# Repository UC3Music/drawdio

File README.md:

# Drawdio

UC3Music version of Drawdio, originally designed by Jay Silver

Double side copper board, big and spacy pads (ready for first-time soldering)

*Uc3Music's enchancement: New output stage to provide twice output voltage and raise volume.*

---------------------------------------

Versión UC3Music del Drawdio, diseñado originalmente por Jay Silver

PCB de doble cara, pads grandes y espaciados (facil de soldar por noveles)

*Mejora de UC3Music: nueva etapa de salida que proporciona el doble de voltaje de salida para conseguir más volumen de salida.*

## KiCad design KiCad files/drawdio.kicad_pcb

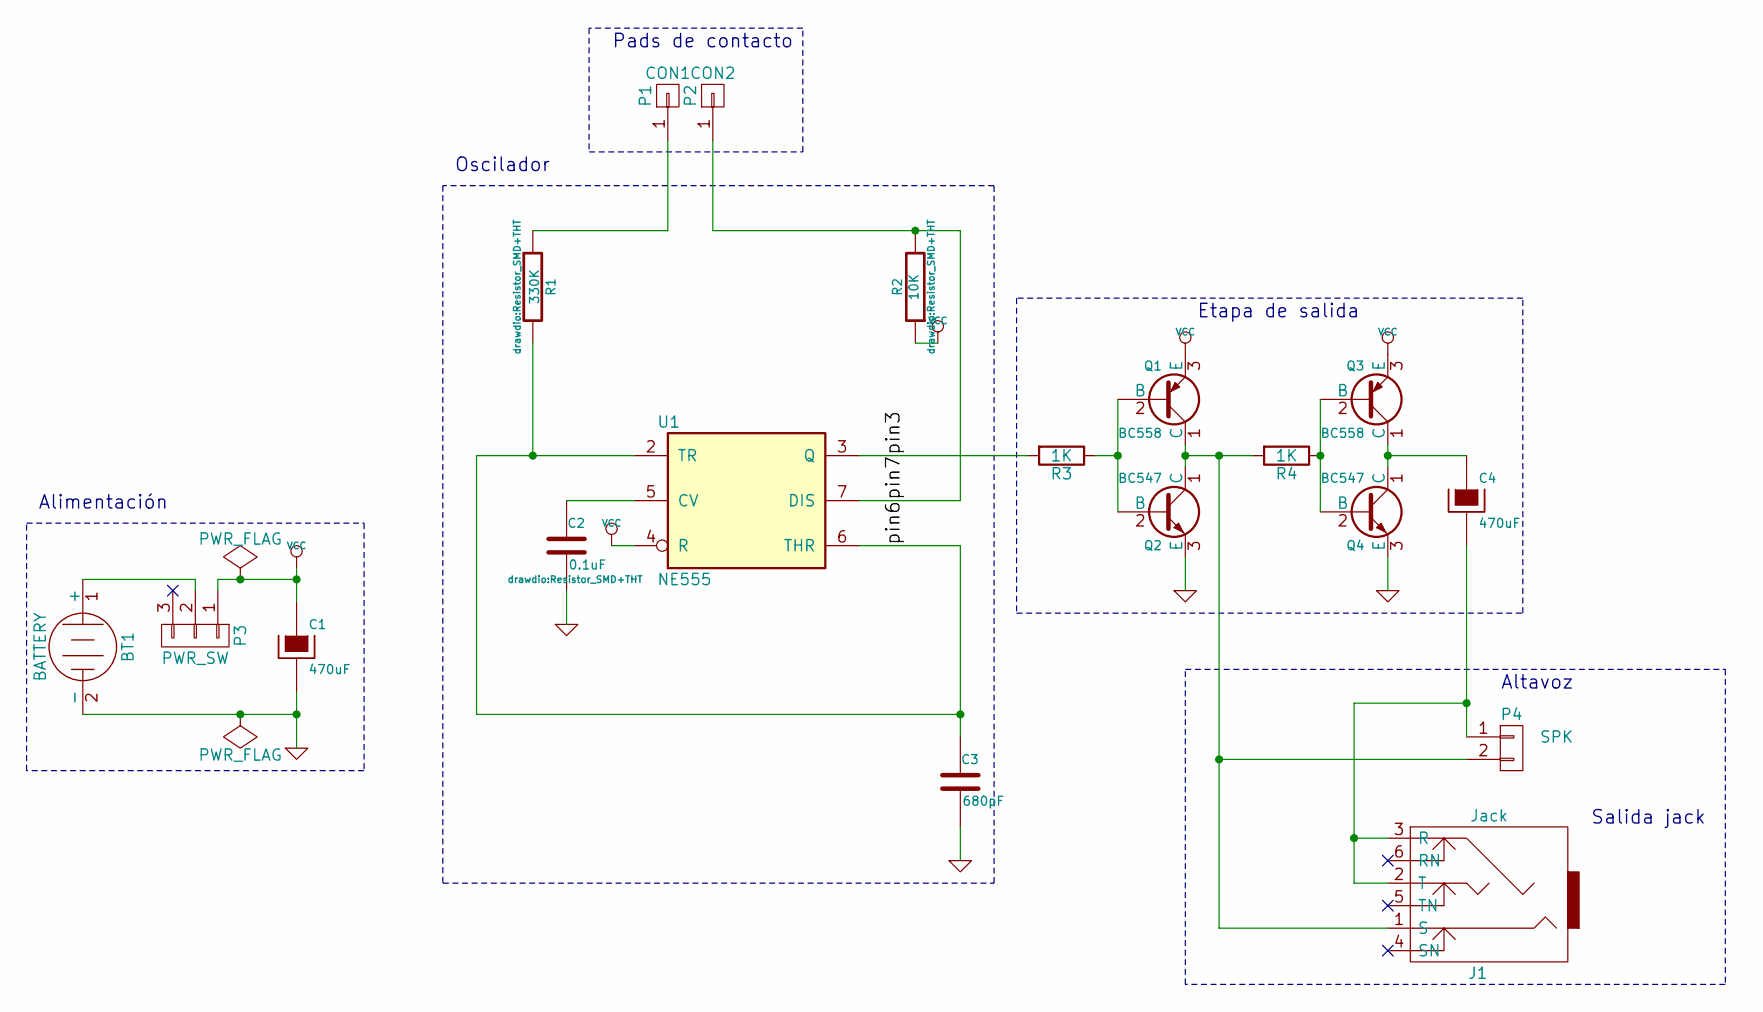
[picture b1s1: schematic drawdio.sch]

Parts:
BT1: BATTERY; AAA_cell_holder
C1, C4: 470uF; Elko_vert_11.2x6.3mm_RM2.5
C2: 0.1uF; Resistor_SMD+THT
C3: 680pF; Resistor_SMD+THT
J1: Jack; jack_barato
P1: CON1; Drawdio_conn
P2: CON2; Drawdio_conn
P3: PWR_SW; PWR_SW_Drawdio_SS-12D00(1P2T)
P4: SPK; RS_mini_speaker_724-3100
Q1, Q3: BC558; TO-92_JorFru_compact
Q2, Q4: BC547; TO-92_JorFru_compact
R1: 330K; Resistor_SMD+THT
R2: 10K; Resistor_SMD+THT
R3, R4: 1K; Resistor_SMD+THT
U1: NE555; DIP8+SOIC8_2

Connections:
/pin3: R3.2, U1.3 (Q)
/pin6: C3.1, R1.2, U1.2 (TR), U1.6 (THR)
/pin7: P2.1, R2.2, U1.7 (DIS)
GND: BT1.2 (-), C1.2, C2.2, C3.2, Q2.3 (E), Q4.3 (E), U1.1 (GND)
unnamed 4: BT1.1 (+), P3.2; also elsewhere on the board
unnamed: C2.1, U1.5 (CV)
unnamed: C4.1, Q3.1 (C), Q4.1 (C)
unnamed: C4.2, J1.2 (T), J1.3 (R), P4.1
unnamed: J1.1 (S), P4.2, Q1.1 (C), Q2.1 (C), R4.2
unnamed: P1.1, R1.1
unnamed: Q1.2 (B), Q2.2 (B), R3.1
unnamed: Q3.2 (B), Q4.2 (B), R4.1
VCC: C1.1, P3.1, Q1.3 (E), Q3.3 (E), R2.1, U1.4 (R), U1.8 (VCC); also elsewhere on the board

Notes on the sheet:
Altavoz
Etapa de salida
Alimentación
Pads de contacto
Oscilador
Salida jack

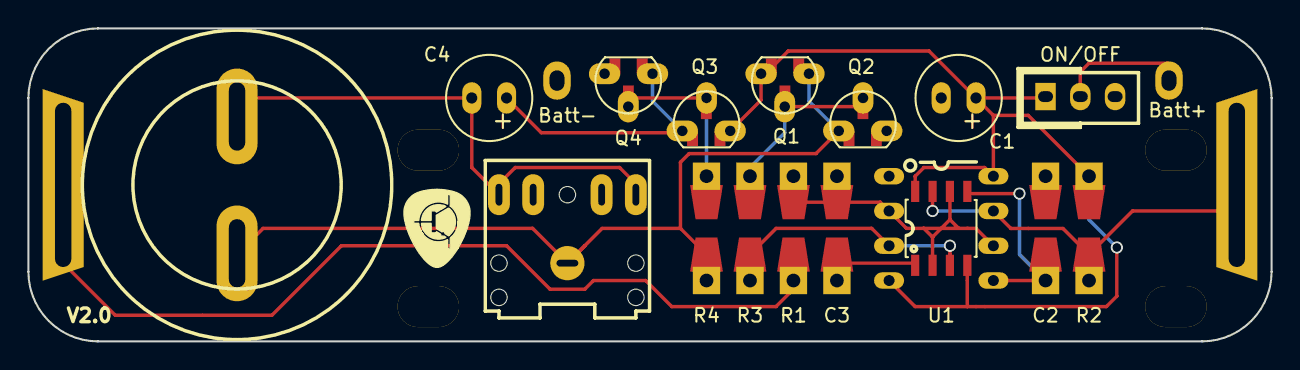
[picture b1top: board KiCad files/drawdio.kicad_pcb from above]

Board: 2 copper layers, 90.8 x 22.9 mm, 20 parts (0 on the bottom side), 13 nets.

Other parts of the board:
ON/OFF: PWR_SW; PWR_SW_Drawdio_SS-12D00(1P2T)
SPK: LOGO; Fiducial_1mm_Dia_2.54mm_Outer_CopperTop

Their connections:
unnamed 4: ON/OFF.2; also elsewhere on the board
VCC: ON/OFF.1; also elsewhere on the board

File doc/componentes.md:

# Condensadores
* C1 470uF
* C2 0.1uF
* C3 680pF
* C4 470uF

# Resistencias
* R1 330K o similar
* R2 10K
* R3, R4 1K

# Transistores
* Q2, Q4 BC547
* Q1, Q3 BC558/7

# Otros
* Muelle del portapilas hacia el lado contrario del altavoz
* Altavoz sin polaridad

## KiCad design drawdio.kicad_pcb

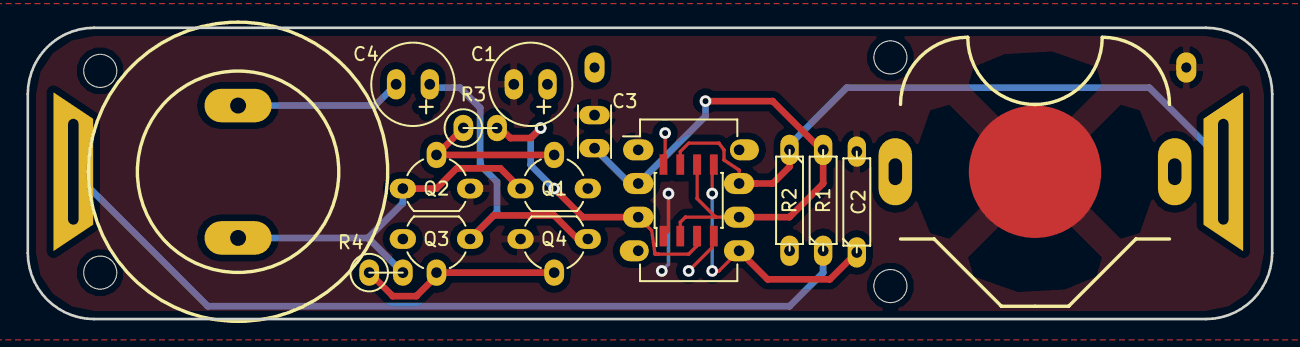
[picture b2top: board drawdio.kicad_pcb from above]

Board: 2 copper layers, 94.0 x 22.0 mm, 23 parts (0 on the bottom side), 12 nets.

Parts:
BT1: BATTERY; CR2025_Keystone_3002_button_cell_holder_SMT
C1, C4: CP; Elko_vert_11.2x6.3mm_RM2.5
C2: C; R3
C3: C; C_Rect_L4_W2.5_P2.5
P1, P2: CONN_01X01; Drawdio_conn
P3, P5, P6, P7: CONN_01X01; MountingHole_2-5mm
P4: CONN_01X02; RS_mini_speaker_724-3100
P9: CONN_02X04; SOIC-8_3.9x4.9mm_Pitch1.27mm
P10: CONN_01X02; AAA_cell_holder
Q1, Q3: BC558; TO-92_Molded_Wide_Oval
Q2, Q4: BC547; TO-92_Molded_Wide_Oval
R1, R2: R; R3
R3, R4: R; R1
U1: LM555N; DIP-8_W7.62mm_LongPads

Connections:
/pin2: C3.1, P9.2, P9.6, R1.2, U1.2, U1.6
/pin3: P9.3, R3.2, U1.3
/pin5: C2.1, P9.5, U1.5
/pin7: P2.1, P9.7, R2.1, U1.7
GND: BT1.2, C1.2, C2.2, C3.2, P9.1, P10.1, Q2.3, Q4.3, U1.1
unnamed: C4.1, Q3.1, Q4.1
unnamed: C4.2, P4.1
unnamed: P1.1, R1.1
unnamed: P4.2, Q1.1, Q2.1, R4.2
unnamed: Q1.2, Q2.2, R3.1
unnamed: Q3.2, Q4.2, R4.1
VCC: BT1.1, C1.1, P9.4, P9.8, P10.2, Q1.3, Q3.3, R2.2, U1.4, U1.8

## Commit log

2015-06-16 prototipo versión amatacaballo
2015-06-16 gerbers add
2015-09-05 Bigger pads for easier soldering
2015-09-05 Trigged size
2015-09-07 smaller board
2015-09-07 V0.2
2015-09-09 added README file
2015-09-09 readme revision
2015-09-09 media revision
2015-09-10 Updated README.md to show image
2015-09-10 Fix ugly track
2015-09-10 Add GND plane in front layer
2015-09-18 Fixed ugly traces
2015-09-18 Update gerbers
2015-10-19 Heavy work
2015-10-19 Added holes
2015-10-27 Añadidas resistencias
2015-10-27 AAA cell added
2015-10-27 Pre-release 1.0
2015-10-28 Reviewed and ready
2015-10-28 Gerbers sent
2015-11-02 Updated README and media folder
2015-11-02 Fixed image
2015-11-02 fixed route
2015-11-15 Wiki is coming
2015-11-15 files moved to folders
2017-01-20 schematic upgrades
2017-01-20 added parts lists with links to RS casta-todavia
2017-01-23 Checkpoint, a dormir!
2017-01-23 Adeed Jack
2017-01-23 Redimensionada
2017-01-25 puede que funcione
2017-01-25 Mounting holes
2017-01-26 Casi terminado
2017-01-27 añadidas silkscreen. Letras y numerajos
2017-01-27 añadidos gerber
2017-01-27 minucias en la silkscreen, resubiendo gerber
2017-01-27 tenia errores el gerber
2017-01-27 presentable V2.0
2017-01-28 añadidas instrucciones
2017-02-06 Retocado el tamaño de algunas silkscreen
2017-08-31 Fix style of README.md
